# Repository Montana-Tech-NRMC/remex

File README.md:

# remex board

Pin layout:

| Function    | Pin         |
| ----------- | ----------- |
| I2C SDA | 4.6 |
| I2C SCL | 4.7 | 
| UART TX | 4.3 |
| UART RX | 4.2 |
| ADC0    | 1.0 |
| ADC1    | 1.1 |
| ADC2    | 1.2 |
| ADC3    | 1.3 |
| QEI0 A  | 1.4 |
| QEI0 B  | 1.5 |
| QEI1 A  | 1.6 |
| QEI1 B  | 1.7 |
| PWM0    | 6.0 |
| PWM1    | 6.1 |

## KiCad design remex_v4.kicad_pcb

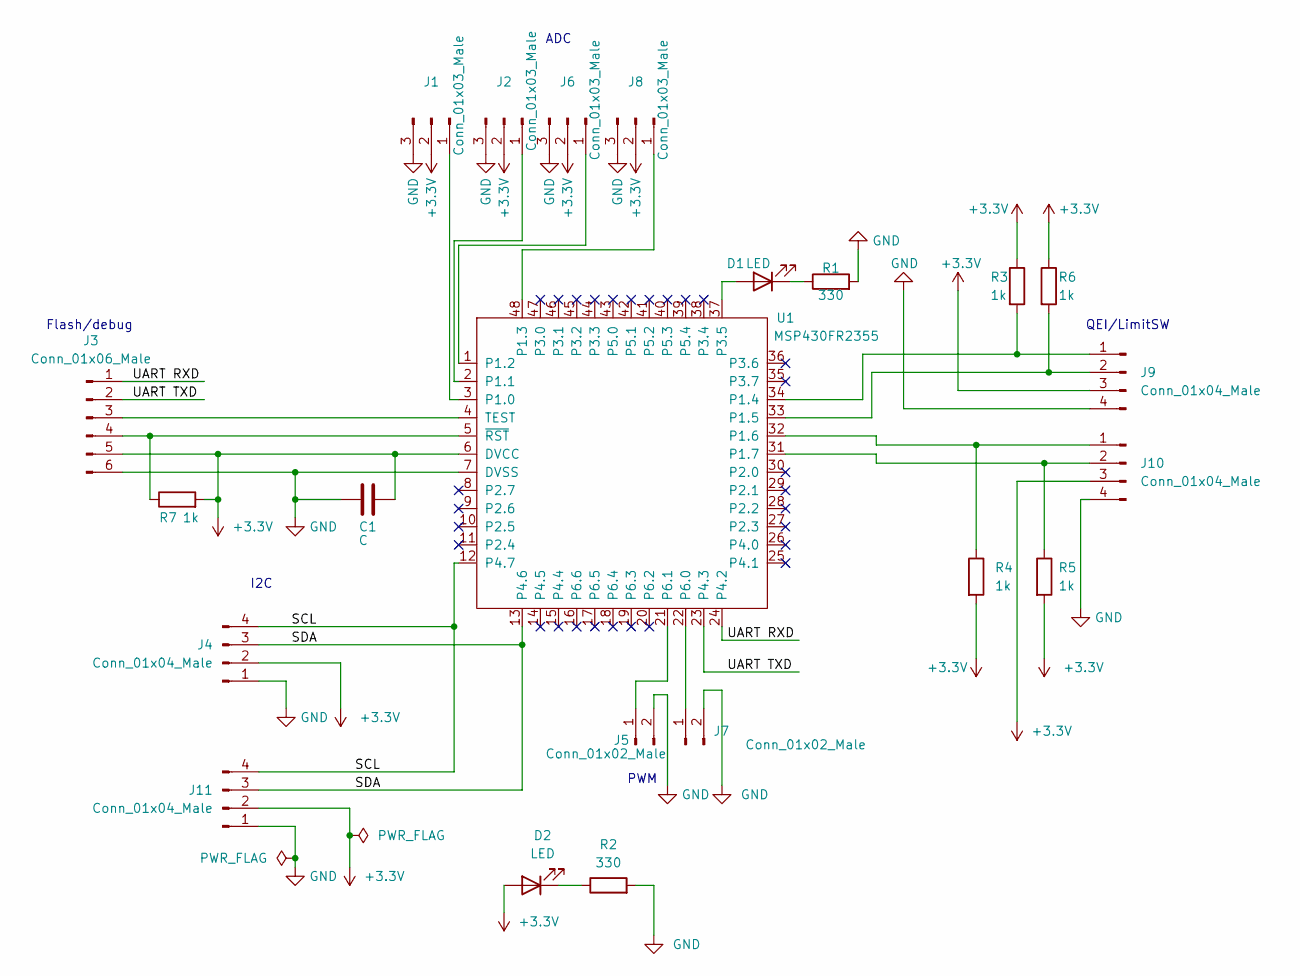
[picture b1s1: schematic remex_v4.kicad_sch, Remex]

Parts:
C1: C; R_0603_1608Metric_Pad0.98x0.95mm_HandSolder
D1, D2: LED; LED_0805_2012Metric
J1, J2, J6, J8: Conn_01x03_Male; Molex_PicoBlade_53261-0371_1x03-1MP_P1.25mm_Horizontal
J3: Conn_01x06_Male; Molex_PicoBlade_53261-0671_1x06-1MP_P1.25mm_Horizontal
J4, J11: Conn_01x04_Male; JST_SH_SM04B-SRSS-TB_1x04-1MP_P1.00mm_Horizontal
J5, J7: Conn_01x02_Male; Molex_PicoBlade_53261-0271_1x02-1MP_P1.25mm_Horizontal
J9, J10: Conn_01x04_Male; Molex_PicoBlade_53261-0471_1x04-1MP_P1.25mm_Horizontal
R1, R2: 330; R_0603_1608Metric_Pad0.98x0.95mm_HandSolder
R3, R4, R5, R6, R7: 1k; R_0603_1608Metric_Pad0.98x0.95mm_HandSolder
U1: MSP430FR2355; LQFP-48_7x7mm_P0.5mm

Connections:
+3.3V: C1.1, D2.2 (A), J1.2, J2.2, J3.5, J4.2, J6.2, J8.2, J9.3, J10.3, J11.2, R3.1, R4.2, R5.2, R6.1, R7.2, U1.6 (DVCC)
/SCL: J4.4, J11.4, U1.12 (P4.7)
/SDA: J4.3, J11.3, U1.13 (P4.6)
/UART RXD: J3.1, U1.24 (P4.2)
/UART TXD: J3.2, U1.23 (P4.3)
GND: C1.2, J1.3, J2.3, J3.6, J4.1, J5.2, J6.3, J7.2, J8.3, J9.4, J10.4, J11.1, R1.2, R2.2, U1.7 (DVSS)
unnamed: D1.1 (K), R1.1
unnamed: D1.2 (A), U1.37 (P3.5)
unnamed: D2.1 (K), R2.1
unnamed: J1.1, U1.3 (P1.0)
unnamed: J2.1, U1.2 (P1.1)
unnamed: J3.3, U1.4 (TEST)
unnamed: J3.4, R7.1, U1.5 (~RST)
unnamed: J5.1, U1.21 (P6.1)
unnamed: J6.1, U1.1 (P1.2)
unnamed: J7.1, U1.22 (P6.0)
unnamed: J8.1, U1.48 (P1.3)
unnamed: J9.1, R3.2, U1.34 (P1.4)
unnamed: J9.2, R6.2, U1.33 (P1.5)
unnamed: J10.1, R4.1, U1.32 (P1.6)
unnamed: J10.2, R5.1, U1.31 (P1.7)

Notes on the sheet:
ADC
QEI/LimitSW
PWM
I2C
Flash/debug

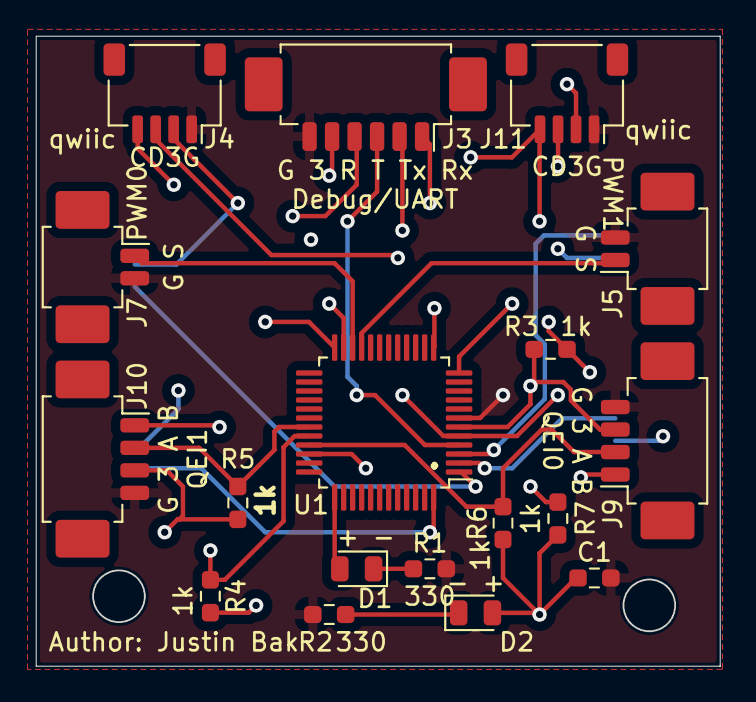
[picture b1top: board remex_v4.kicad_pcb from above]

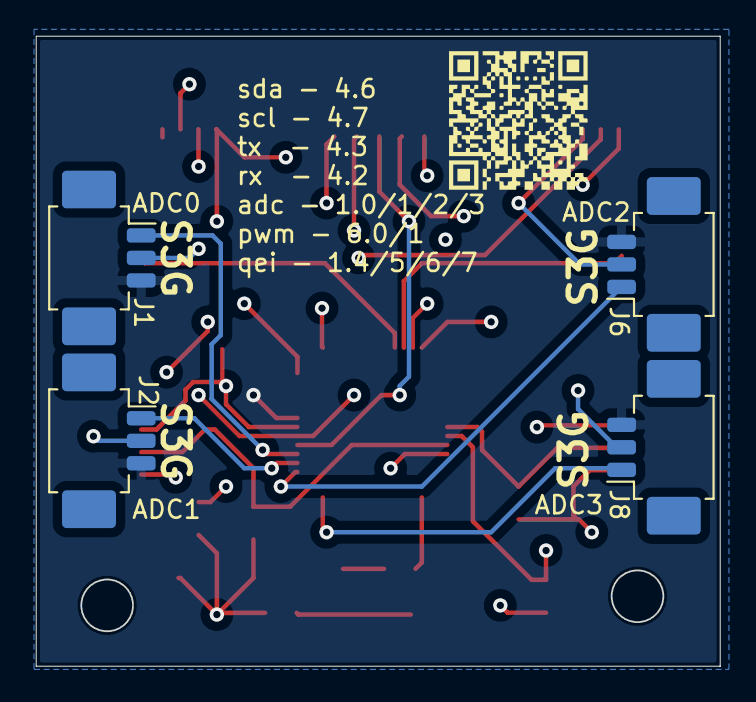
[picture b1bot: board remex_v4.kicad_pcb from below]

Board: 4 copper layers, 37.9 x 34.9 mm, 22 parts (4 on the bottom side), 21 nets.

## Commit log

2023-01-25 gitignore
2023-01-25 init
2023-01-25 added qr to link to the repo
2023-02-14 Corrected qwiic orientation, added silkscreen details, changed diodes to 0805, fixed bugs with qei
2023-02-18 silkscreen typo
2023-04-07 prepare for release
